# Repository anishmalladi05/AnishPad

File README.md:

# AnishPad
I made this Macropad because I wanted one that was more customizable then my last, which only had 4 buttons. That time, the rotary encoder got the better of me, so I wanted to successfully put one in this time, which I did!
<br></br>
A 5 key, 1 rotary encoder, and 128 x 32 oled display macropad.

# Images:

<br></br>
# To Flash:
Put the microcontroller in bootloader mode. (Hold reset, double press boot, release reset)
<br></br>
Plug into computer
<br></br>
Drag UF2 file into microcontroller
<br></br>

Replace boot_out.txt with boot_out.txt in my gihub repo under CIRCUITPY FILES
<br></br>
Replace code.py with code.py from my repo
<br></br>
Add boot.txt from my repo
<br></br>
Add boot.py from my repo
<br></br>

It should start working!

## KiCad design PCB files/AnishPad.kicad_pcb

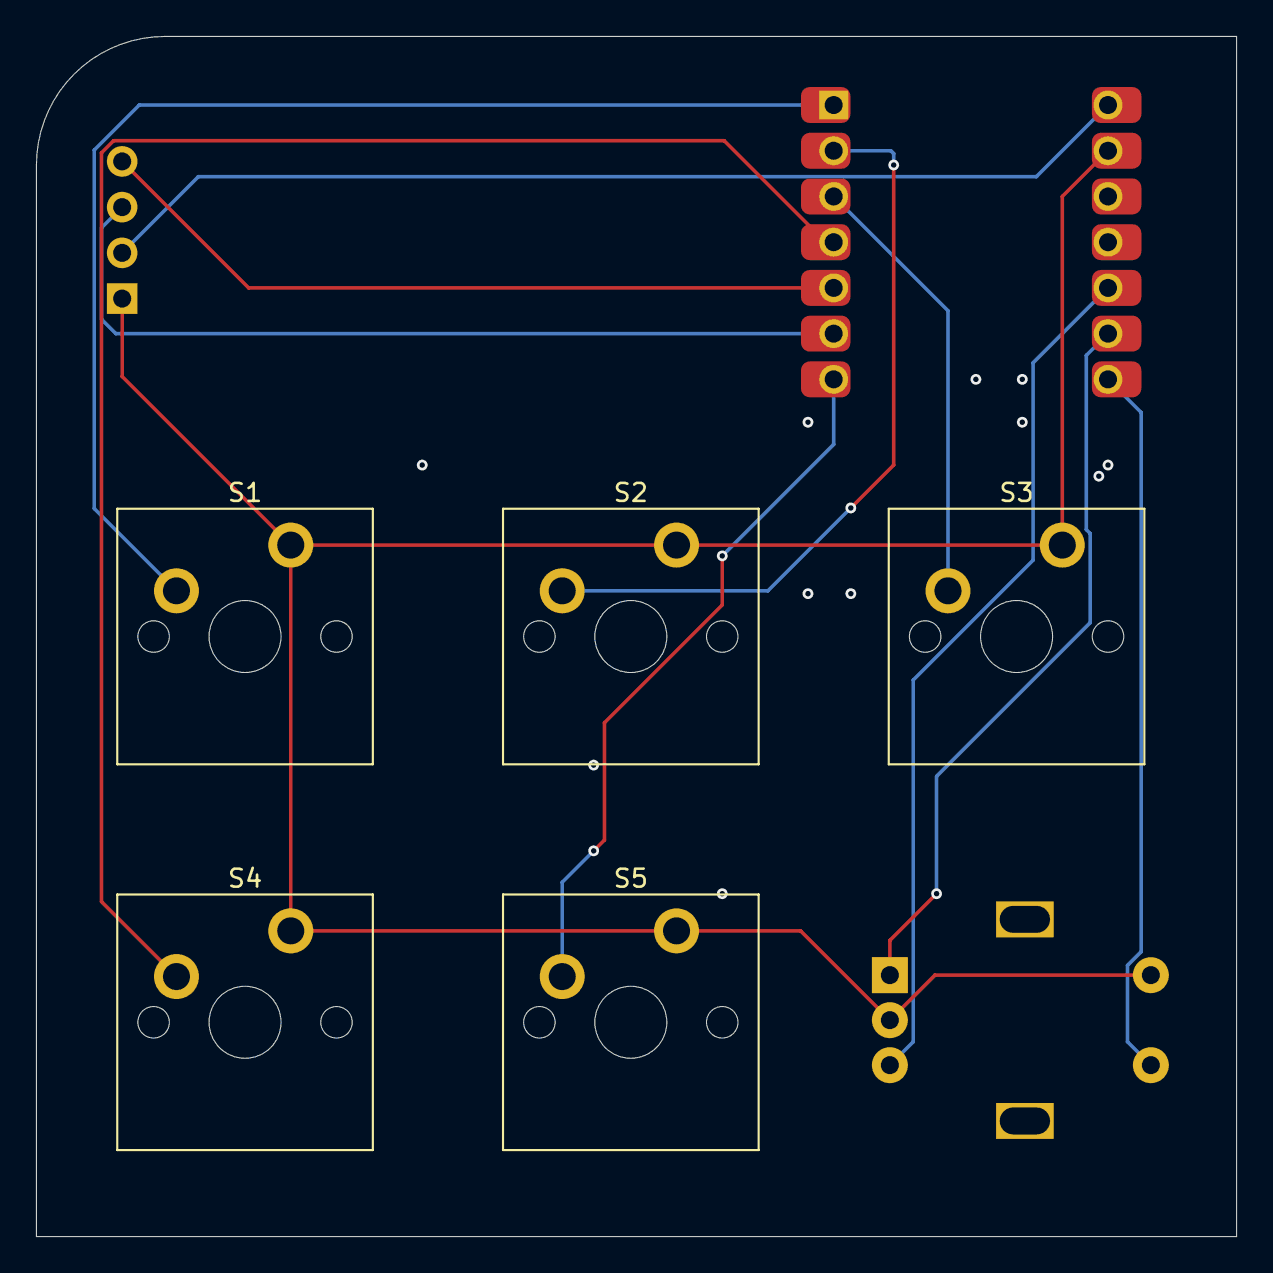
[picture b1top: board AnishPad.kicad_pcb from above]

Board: 2 copper layers, 66.7 x 66.7 mm, 8 parts (0 on the bottom side), 12 nets.

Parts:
J1: OLED_128x32
S1, S2, S3, S4, S5: MX_PCB_1.00u
SW6: RotaryEncoder_Switch; Encoder_EC11_MX
U1: MOUDLE-SEEEDUINO-XIAO; Seeed_XIAO_RP2040

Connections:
1: S1.1, U1.1 (PA02_A0_D0)
2: S2.1, U1.2 (PA4_A1_D1)
3: S3.1, U1.3 (PA10_A2_D2)
4: S4.1, U1.4 (PA11_A3_D3)
5: J1.4 (SDA), U1.5 (PA8_A4_D4_SDA)
6: J1.3 (SCL), U1.6 (PA9_A5_D5_SCL)
7: S5.1, U1.7 (PB08_A6_D6_TX)
8: SW6.S1, U1.8 (PB09_A7_D7_RX)
9: SW6.A, U1.9 (PA7_A8_D8_SCK)
10: SW6.B, U1.10 (PA5_A9_D9_MISO)
13: J1.1 (GND), S1.2, S2.2, S3.2, S4.2, S5.2, SW6.C, SW6.S2, U1.13 (GND)
14: J1.2 (VCC), U1.14 (5V)
